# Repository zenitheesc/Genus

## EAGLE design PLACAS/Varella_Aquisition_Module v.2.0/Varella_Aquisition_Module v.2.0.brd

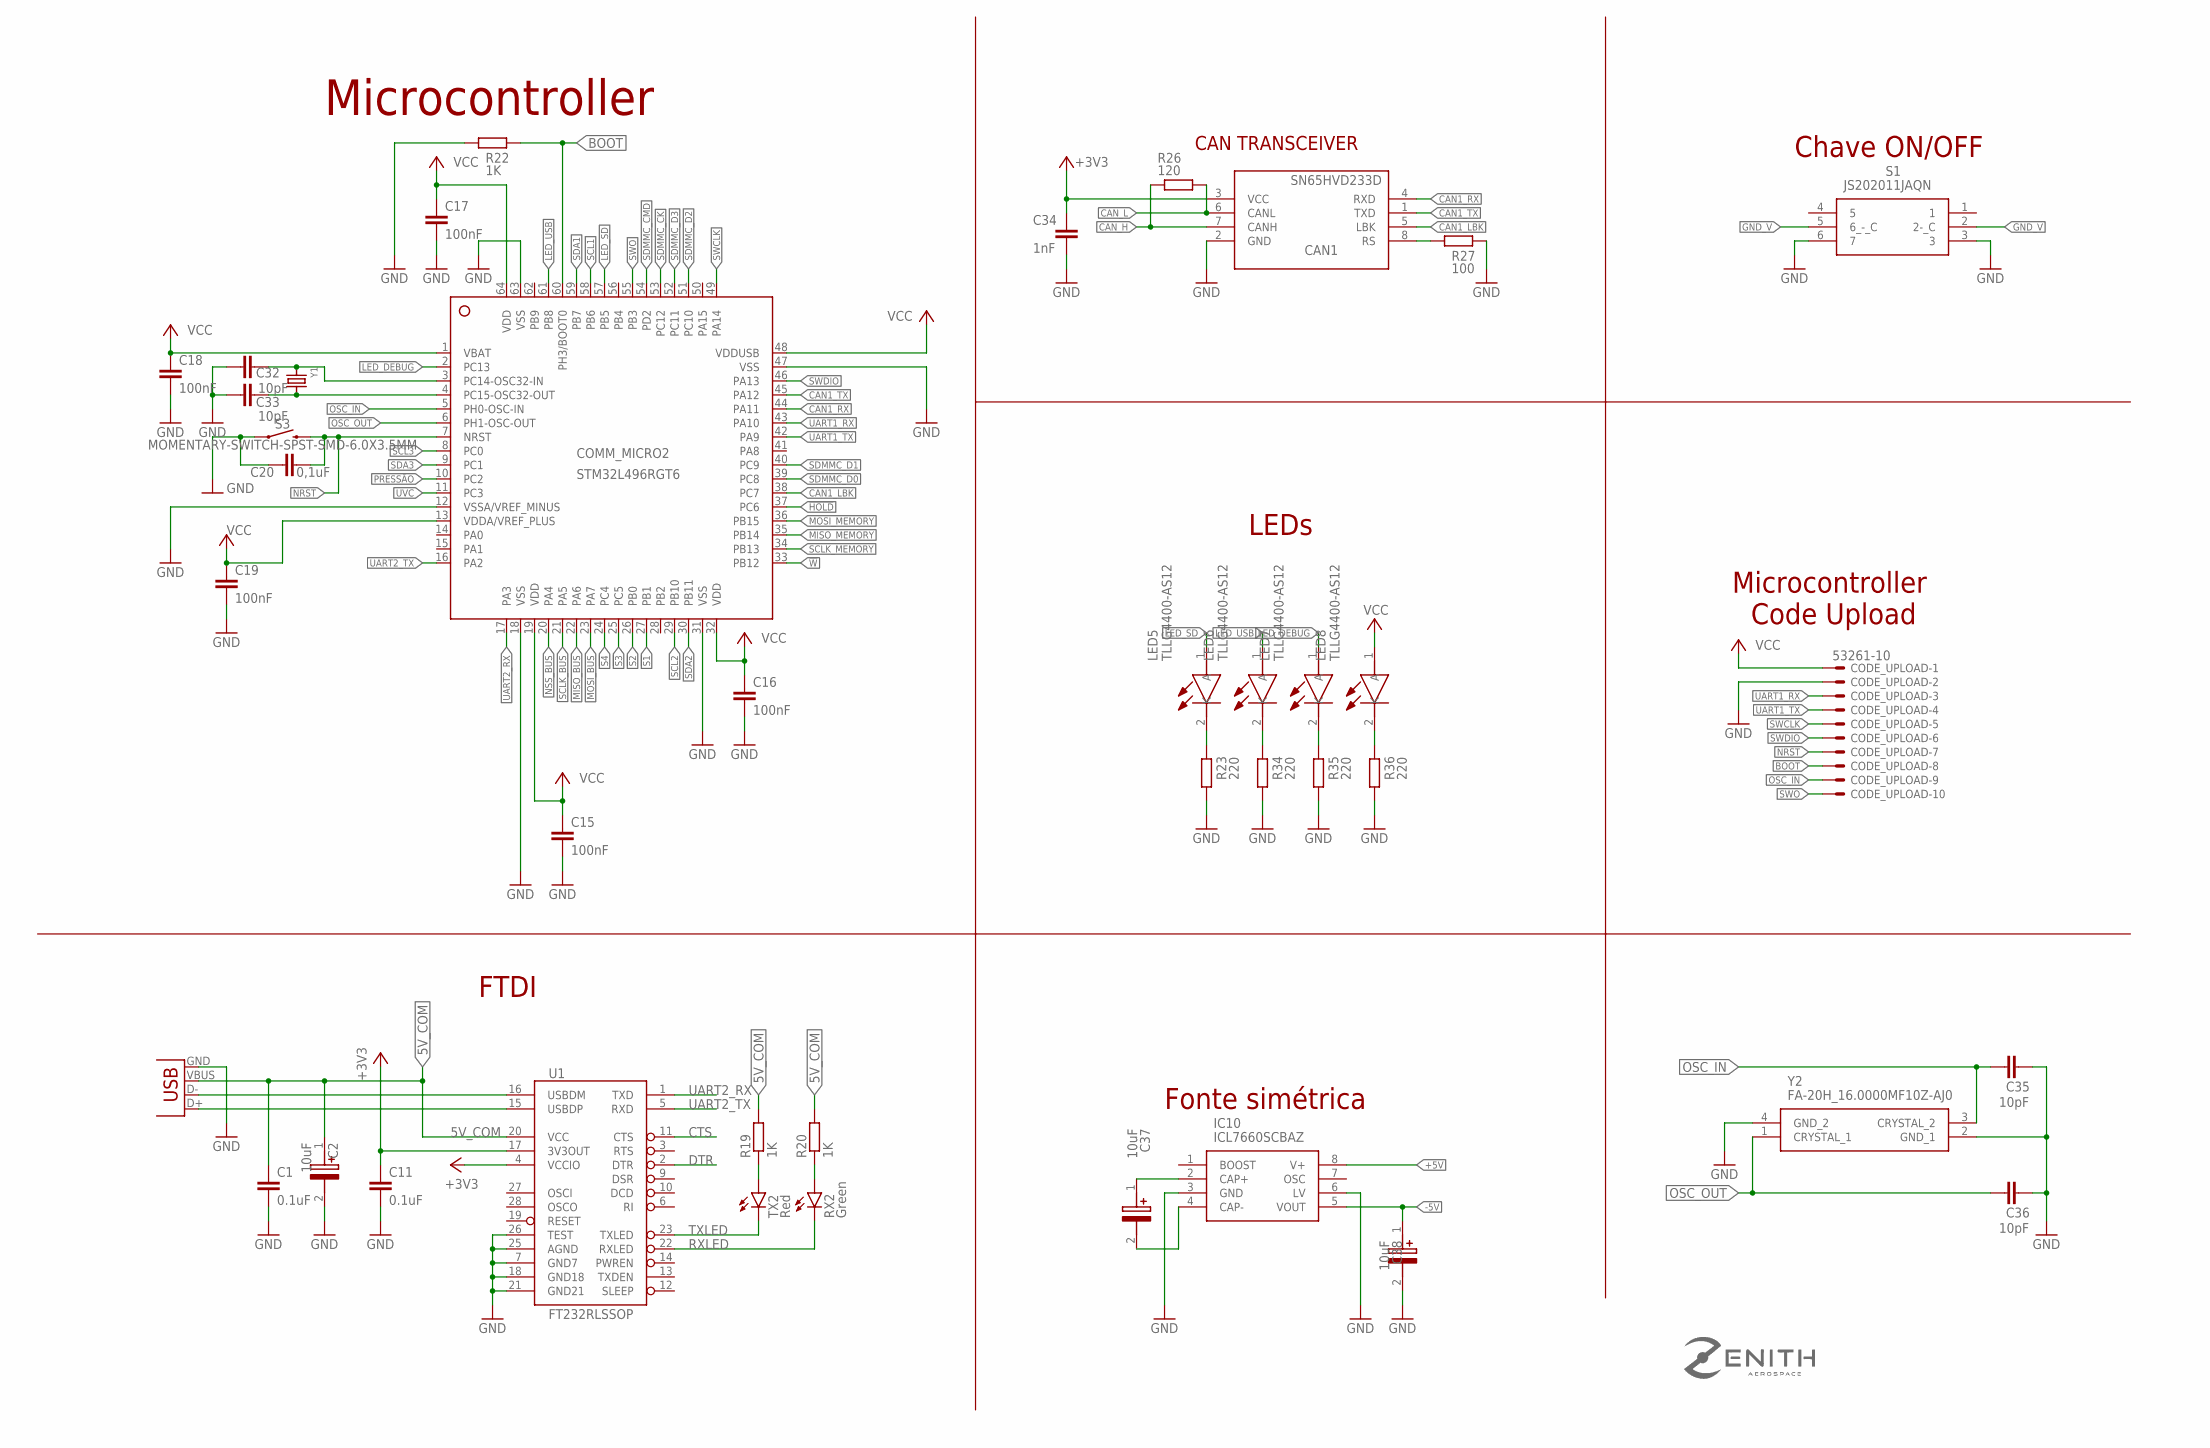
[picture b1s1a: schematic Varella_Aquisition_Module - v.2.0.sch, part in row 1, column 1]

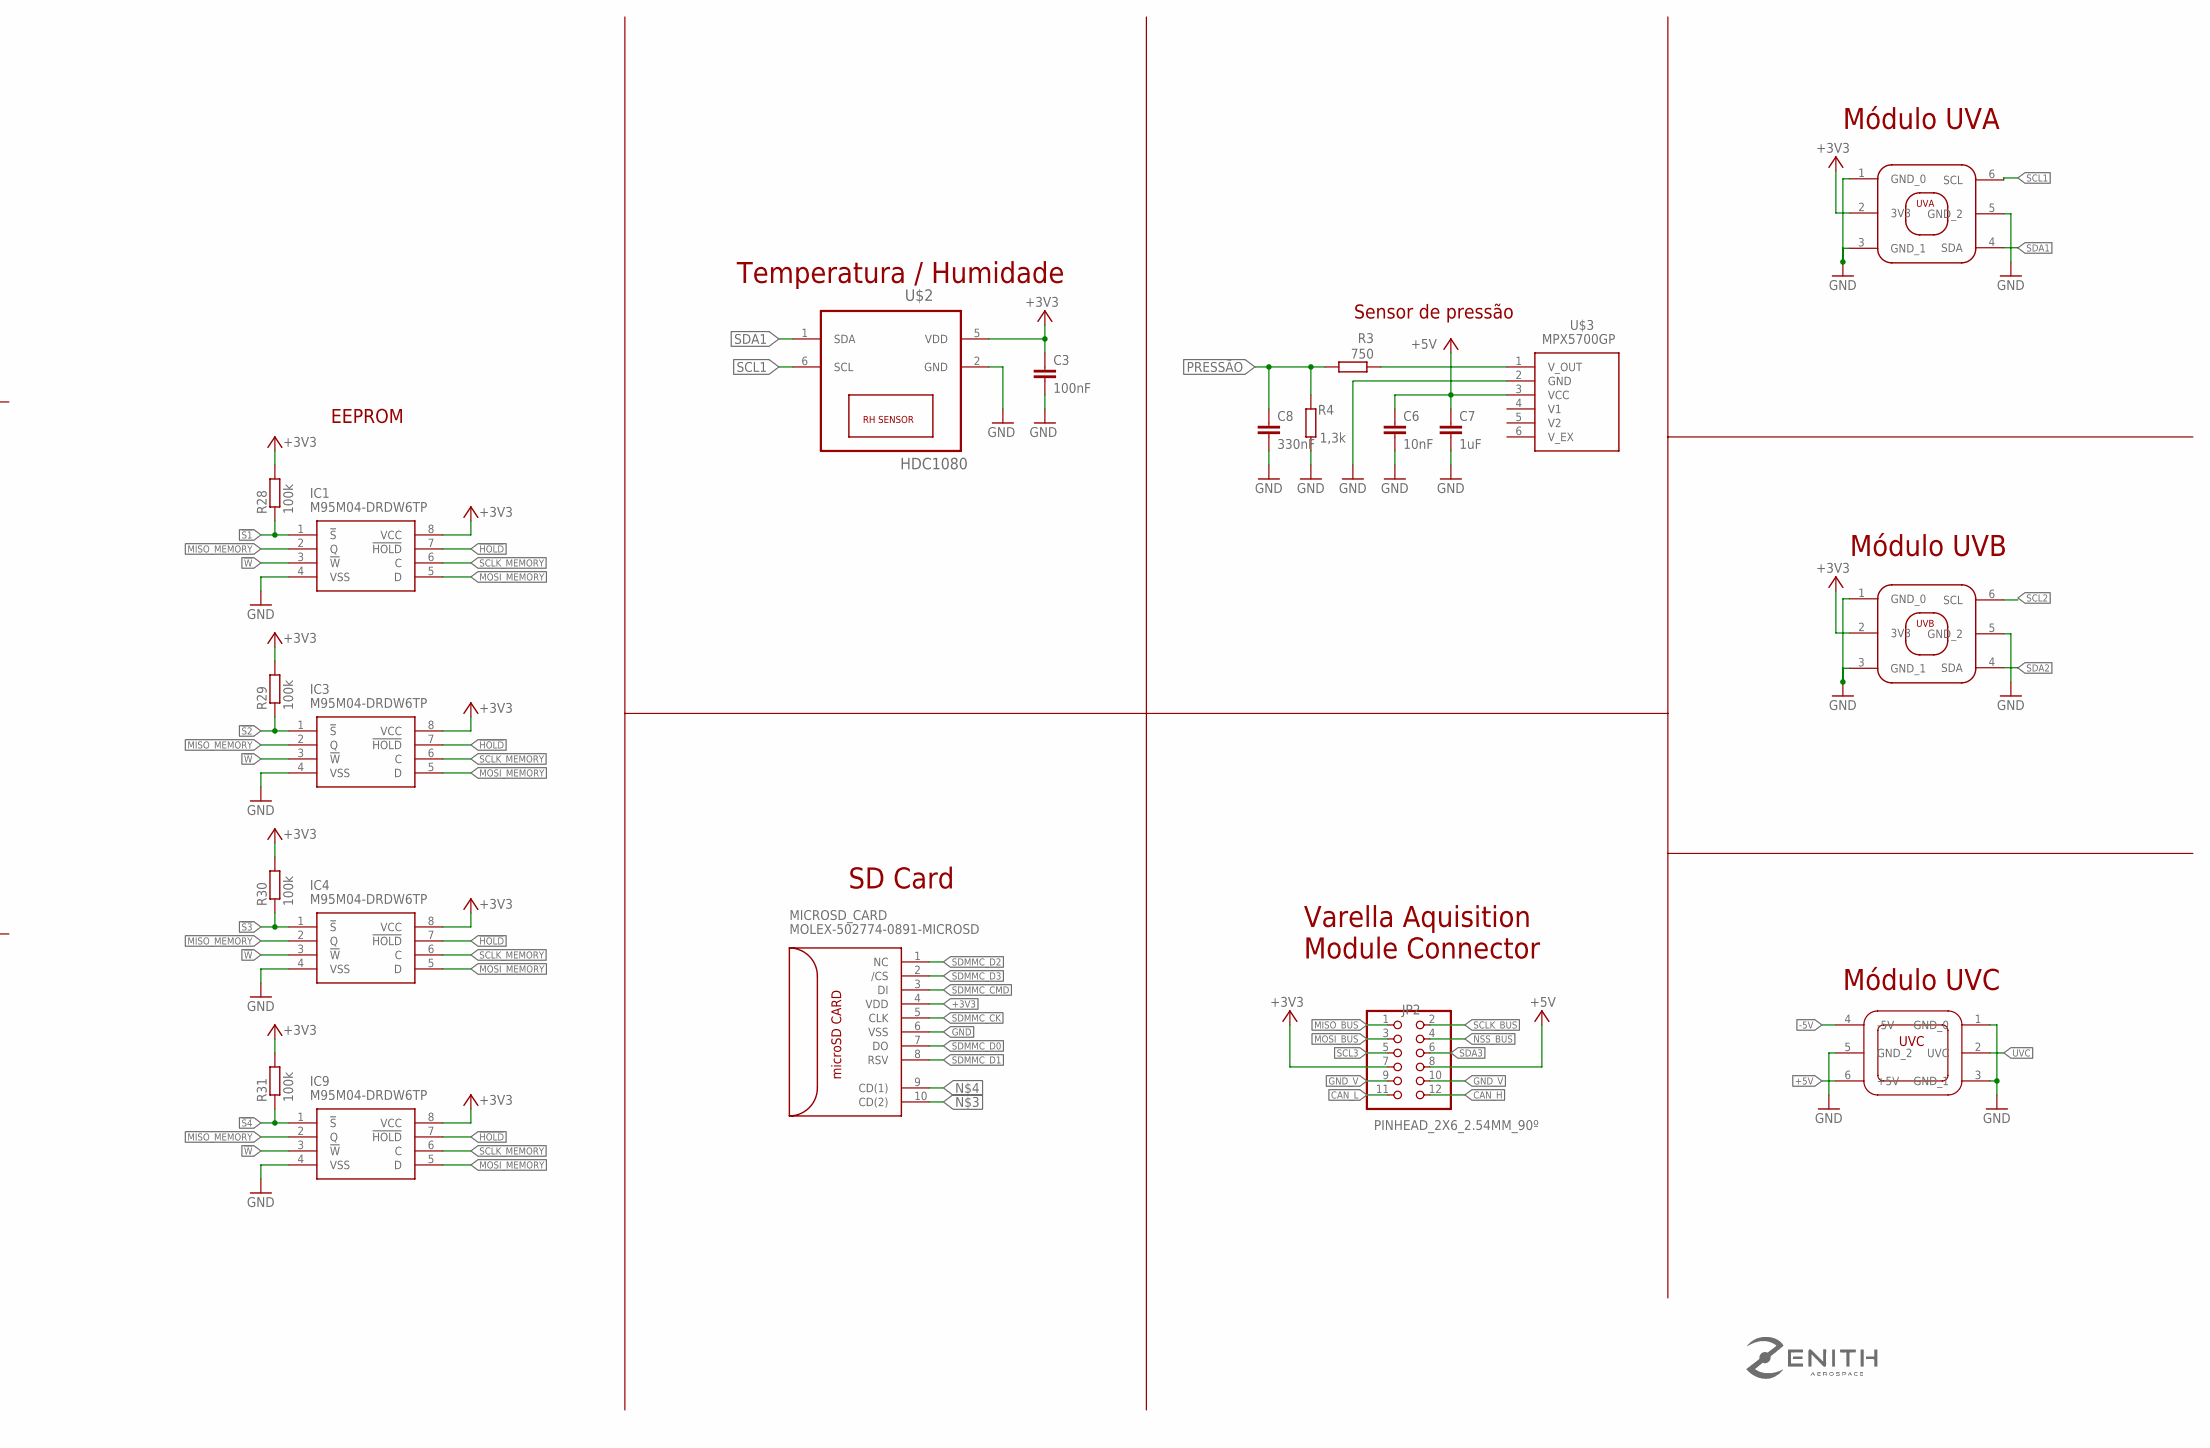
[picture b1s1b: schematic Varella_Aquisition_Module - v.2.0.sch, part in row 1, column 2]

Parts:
C1, C11: 0.1uF; C0805
C2, C37, C38: 10uF; CAPAE430X610N
C3, C15, C16, C17, C18, C19: 100nF; C0805
C6: 10nF; C0805
C7: 1uF; C0805
C8: 330nF; C0805
C20: 0,1uF; C0805
C32, C33, C35, C36: 10pF; C0805
C34: 1nF; C1206
CAN1: SN65HVD233D; SOIC8
CODE_UPLOAD: 53261-10
COMM_MICRO2: STM32L496RGT6; LQFP64_10X10
IC1, IC3, IC4, IC9: M95M04-DRDW6TP; SOP65P640X120-8N
IC10: ICL7660SCBAZ; SOIC127P600X175-8N@1
JP2: PINHEAD_2X6_2.54MM_90º
LED5, LED6, LED7, LED8: TLLG4400-AS12; TLLG4400AS12
MICROSD_CARD: MOLEX-502774-0891-MICROSD
R3: 750; R0805
R4: 1,3k; R0805
R19, R20, R22: 1K; R0805
R23, R34, R35, R36: 220; R0805
R26: 120; R1206
R27: 100; R0805
R28, R29, R30, R31: 100k; R0805
RX2: Green; CHIPLED_0805
S1: JS202011JAQN
S3: MOMENTARY-SWITCH-SPST-SMD-6.0X3.5MM; TACTILE_SWITCH_SMD_6.0X3.5MM
TX2: Red; CHIPLED_0805
U1: FT232RLSSOP; SSOP28DB
U$1: UVA_MODULE
U$2: HDC1080; TI-S-PWSON-N6
U$3: MPX5700GP
U$4: UVB_MODULE
U$5: UVC_MODULE
X2: USB-SMD-NS; USB-MINIB-NOSTOP
Y1: CRYSTAL8X3.8SMT; CRYSTAL_8X3.8
Y2: FA-20H_16.0000MF10Z-AJ0; FA20H160000MF12ZAC3

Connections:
5V_COM: C1.1, C2.1 (+), R19.2, R20.2, U1.20 (VCC), X2.VBUS
!HOLD: COMM_MICRO2.37 (PC6), IC1.7 (!HOLD), IC3.7 (!HOLD), IC4.7 (!HOLD), IC9.7 (!HOLD)
!S1: COMM_MICRO2.27 (PB1), IC1.1 (!S), R28.1
!S2: COMM_MICRO2.26 (PB0), IC3.1 (!S), R29.1
!S3: COMM_MICRO2.25 (PC5), IC4.1 (!S), R30.1
!S4: COMM_MICRO2.24 (PC4), IC9.1 (!S), R31.1
!W: COMM_MICRO2.33 (PB12), IC1.3 (!W), IC3.3 (!W), IC4.3 (!W), IC9.3 (!W)
+3V3: C3.1, C11.1, C15.1, C16.1, C17.1, C18.1, C19.1, C34.1, CAN1.3 (VCC), CODE_UPLOAD.1, COMM_MICRO2.1 (VBAT), COMM_MICRO2.13 (VDDA/VREF_PLUS), COMM_MICRO2.19 (VDD), COMM_MICRO2.32 (VDD), COMM_MICRO2.48 (VDDUSB), COMM_MICRO2.64 (VDD), IC1.8 (VCC), IC3.8 (VCC), IC4.8 (VCC), IC9.8 (VCC), JP2.7, LED8.1 (A), MICROSD_CARD.4 (VDD), R28.2, R29.2, R30.2, R31.2, U1.4 (VCCIO), U1.17 (3V3OUT), U$1.2 (3V3), U$2.5 (VDD), U$4.2 (3V3)
+5V: C6.1, C7.1, IC10.8 (V+), JP2.8, U$3.3 (VCC), U$5.6 (+5V)
-5V: C38.1 (+), IC10.5 (VOUT), U$5.4 (-5V)
BOOT: CODE_UPLOAD.8, COMM_MICRO2.60 (PH3/BOOT0), R22.1
CAN1_LBK: CAN1.5 (LBK), COMM_MICRO2.38 (PC7)
CAN1_RX: CAN1.4 (RXD), COMM_MICRO2.44 (PA11)
CAN1_TX: CAN1.1 (TXD), COMM_MICRO2.45 (PA12)
CAN_H: CAN1.7 (CANH), JP2.12, R26.1
CAN_L: CAN1.6 (CANL), JP2.11, R26.2
CRYSTAL1: C32.2, COMM_MICRO2.3 (PC14-OSC32-IN), Y1.P$1 (1)
CTS: U1.11 (CTS)
DTR: U1.2 (DTR)
GND: C1.2, C2.2 (-), C3.2, C6.2, C7.2, C8.2, C11.2, C15.2, C16.2, C17.2, C18.2, C19.2, C20.1, C32.1, C33.1, C34.2, C35.2, C36.2, C38.2 (-), CAN1.2 (GND), CODE_UPLOAD.2, COMM_MICRO2.12 (VSSA/VREF_MINUS), COMM_MICRO2.18 (VSS), COMM_MICRO2.31 (VSS), COMM_MICRO2.47 (VSS), COMM_MICRO2.63 (VSS), IC1.4 (VSS), IC3.4 (VSS), IC4.4 (VSS), IC9.4 (VSS), IC10.3 (GND), IC10.6 (LV), MICROSD_CARD.6 (VSS), R4.2, R22.2, R23.1, R27.1, R34.1, R35.1, R36.1, S1.3, S1.6 (7), S3.1, U1.7 (GND7), U1.18 (GND18), U1.21 (GND21), U1.25 (AGND), U1.26 (TEST), U$1.1 (GND_0), U$1.3 (GND_1), U$1.5 (GND_2), U$2.2 (GND), U$4.1 (GND_0), U$4.3 (GND_1), U$4.5 (GND_2), U$5.1 (GND_0), U$5.3 (GND_1), U$5.5 (GND_2), X2.GND, Y2.2 (GND_1), Y2.4 (GND_2)
GND_V: JP2.9, JP2.10, S1.2 (2-_C), S1.5 (6_-_C)
LED_DEBUG: COMM_MICRO2.2 (PC13), LED7.1 (A)
LED_SD: COMM_MICRO2.57 (PB5), LED5.1 (A)
LED_USB: COMM_MICRO2.61 (PB8), LED6.1 (A)
MISO_BUS: COMM_MICRO2.22 (PA6), JP2.1
MISO_MEMORY: COMM_MICRO2.35 (PB14), IC1.2 (Q), IC3.2 (Q), IC4.2 (Q), IC9.2 (Q)
MOSI_BUS: COMM_MICRO2.23 (PA7), JP2.3
MOSI_MEMORY: COMM_MICRO2.36 (PB15), IC1.5 (D), IC3.5 (D), IC4.5 (D), IC9.5 (D)
unnamed: R3.1, U$3.1 (V_OUT)
unnamed: C33.2, COMM_MICRO2.4 (PC15-OSC32-OUT), Y1.P$4 (2)
unnamed: CAN1.8 (RS), R27.2
unnamed: C37.1 (+), IC10.2 (CAP+)
unnamed: C37.2 (-), IC10.4 (CAP-)
unnamed: LED5.2 (K), R23.2
unnamed: LED6.2 (K), R34.2
unnamed: LED7.2 (K), R35.2
unnamed: LED8.2 (K), R36.2
NRST: C20.2, CODE_UPLOAD.7, COMM_MICRO2.7 (NRST), S3.2
NSS_BUS: COMM_MICRO2.20 (PA4), JP2.4
OSC_IN: C35.1, CODE_UPLOAD.9, COMM_MICRO2.5 (PH0-OSC-IN), Y2.3 (CRYSTAL_2)
OSC_OUT: C36.1, COMM_MICRO2.6 (PH1-OSC-OUT), Y2.1 (CRYSTAL_1)
PRESSÃO: C8.1, COMM_MICRO2.10 (PC2), R3.2, R4.1
RXL: R20.1, RX2.A
RXLED: RX2.C, U1.22 (RXLED)
SCL1: COMM_MICRO2.58 (PB6), U$1.6 (SCL), U$2.6 (SCL)
SCL2: COMM_MICRO2.29 (PB10), U$4.6 (SCL)
SCL3: COMM_MICRO2.8 (PC0), JP2.5
SCLK_BUS: COMM_MICRO2.21 (PA5), JP2.2
SCLK_MEMORY: COMM_MICRO2.34 (PB13), IC1.6 (C), IC3.6 (C), IC4.6 (C), IC9.6 (C)
SDA1: COMM_MICRO2.59 (PB7), U$1.4 (SDA), U$2.1 (SDA)
SDA2: COMM_MICRO2.30 (PB11), U$4.4 (SDA)
SDA3: COMM_MICRO2.9 (PC1), JP2.6
SDMMC_CK: COMM_MICRO2.53 (PC12), MICROSD_CARD.5 (CLK)
SDMMC_CMD: COMM_MICRO2.54 (PD2), MICROSD_CARD.3 (DI)
SDMMC_D0: COMM_MICRO2.39 (PC8), MICROSD_CARD.7 (DO)
SDMMC_D1: COMM_MICRO2.40 (PC9), MICROSD_CARD.8 (RSV)
SDMMC_D2: COMM_MICRO2.51 (PC10), MICROSD_CARD.1 (NC)
SDMMC_D3: COMM_MICRO2.52 (PC11), MICROSD_CARD.2 (/CS)
SWCLK: CODE_UPLOAD.5, COMM_MICRO2.49 (PA14)
SWDIO: CODE_UPLOAD.6, COMM_MICRO2.46 (PA13)
SWO: CODE_UPLOAD.10, COMM_MICRO2.55 (PB3)
TXL: R19.1, TX2.A
TXLED: TX2.C, U1.23 (TXLED)
UART1_RX: CODE_UPLOAD.3, COMM_MICRO2.43 (PA10)
UART1_TX: CODE_UPLOAD.4, COMM_MICRO2.42 (PA9)
UART2_RX: COMM_MICRO2.17 (PA3), U1.1 (TXD)
UART2_TX: COMM_MICRO2.16 (PA2), U1.5 (RXD)
USB_D+2: U1.15 (USBDP), X2.D+
USB_D-2: U1.16 (USBDM), X2.D-
UVC: COMM_MICRO2.11 (PC3), U$5.2 (UVC)

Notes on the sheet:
C:/Users/marcu/Desktop/Ensino Superior/Graduação - Eng Elétrica/Zenith/zenith-v2.bmp
Microcontroller
CAN TRANSCEIVER
Microcontroller Code Upload
SD Card
Varella Aquisition Module Connector
EEPROM
FTDI
Temperatura / Humidade
Fonte simétrica
LEDs
Sensor de pressão
Chave ON/OFF
Módulo UVA
Módulo UVB
Módulo UVC

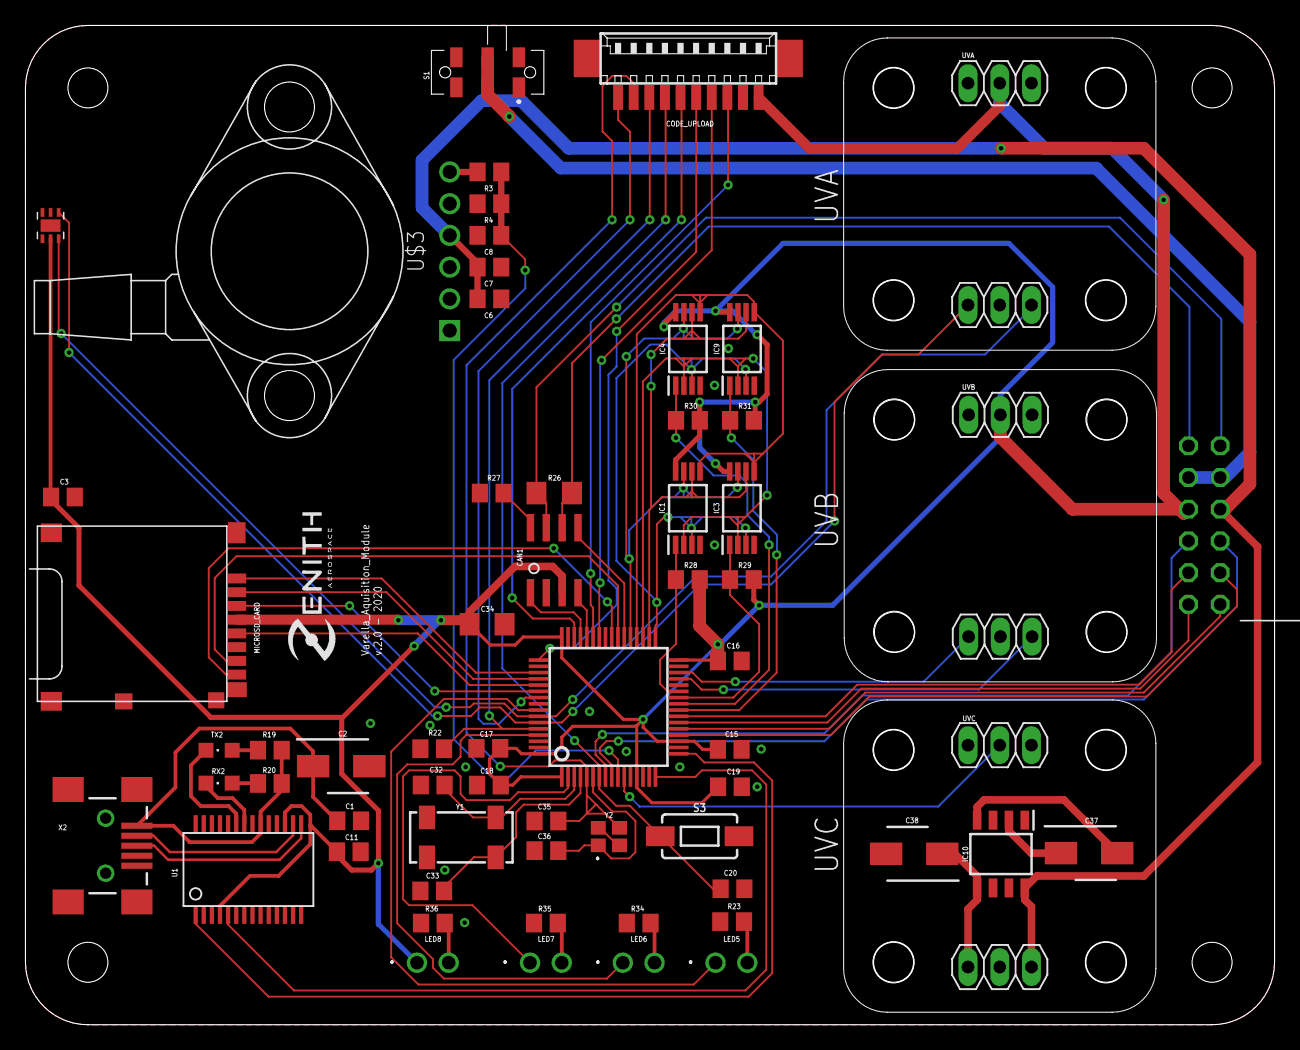
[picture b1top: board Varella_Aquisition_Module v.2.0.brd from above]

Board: 2 copper layers, 100.0 x 80.0 mm, 62 parts (1 on the bottom side), 68 nets.

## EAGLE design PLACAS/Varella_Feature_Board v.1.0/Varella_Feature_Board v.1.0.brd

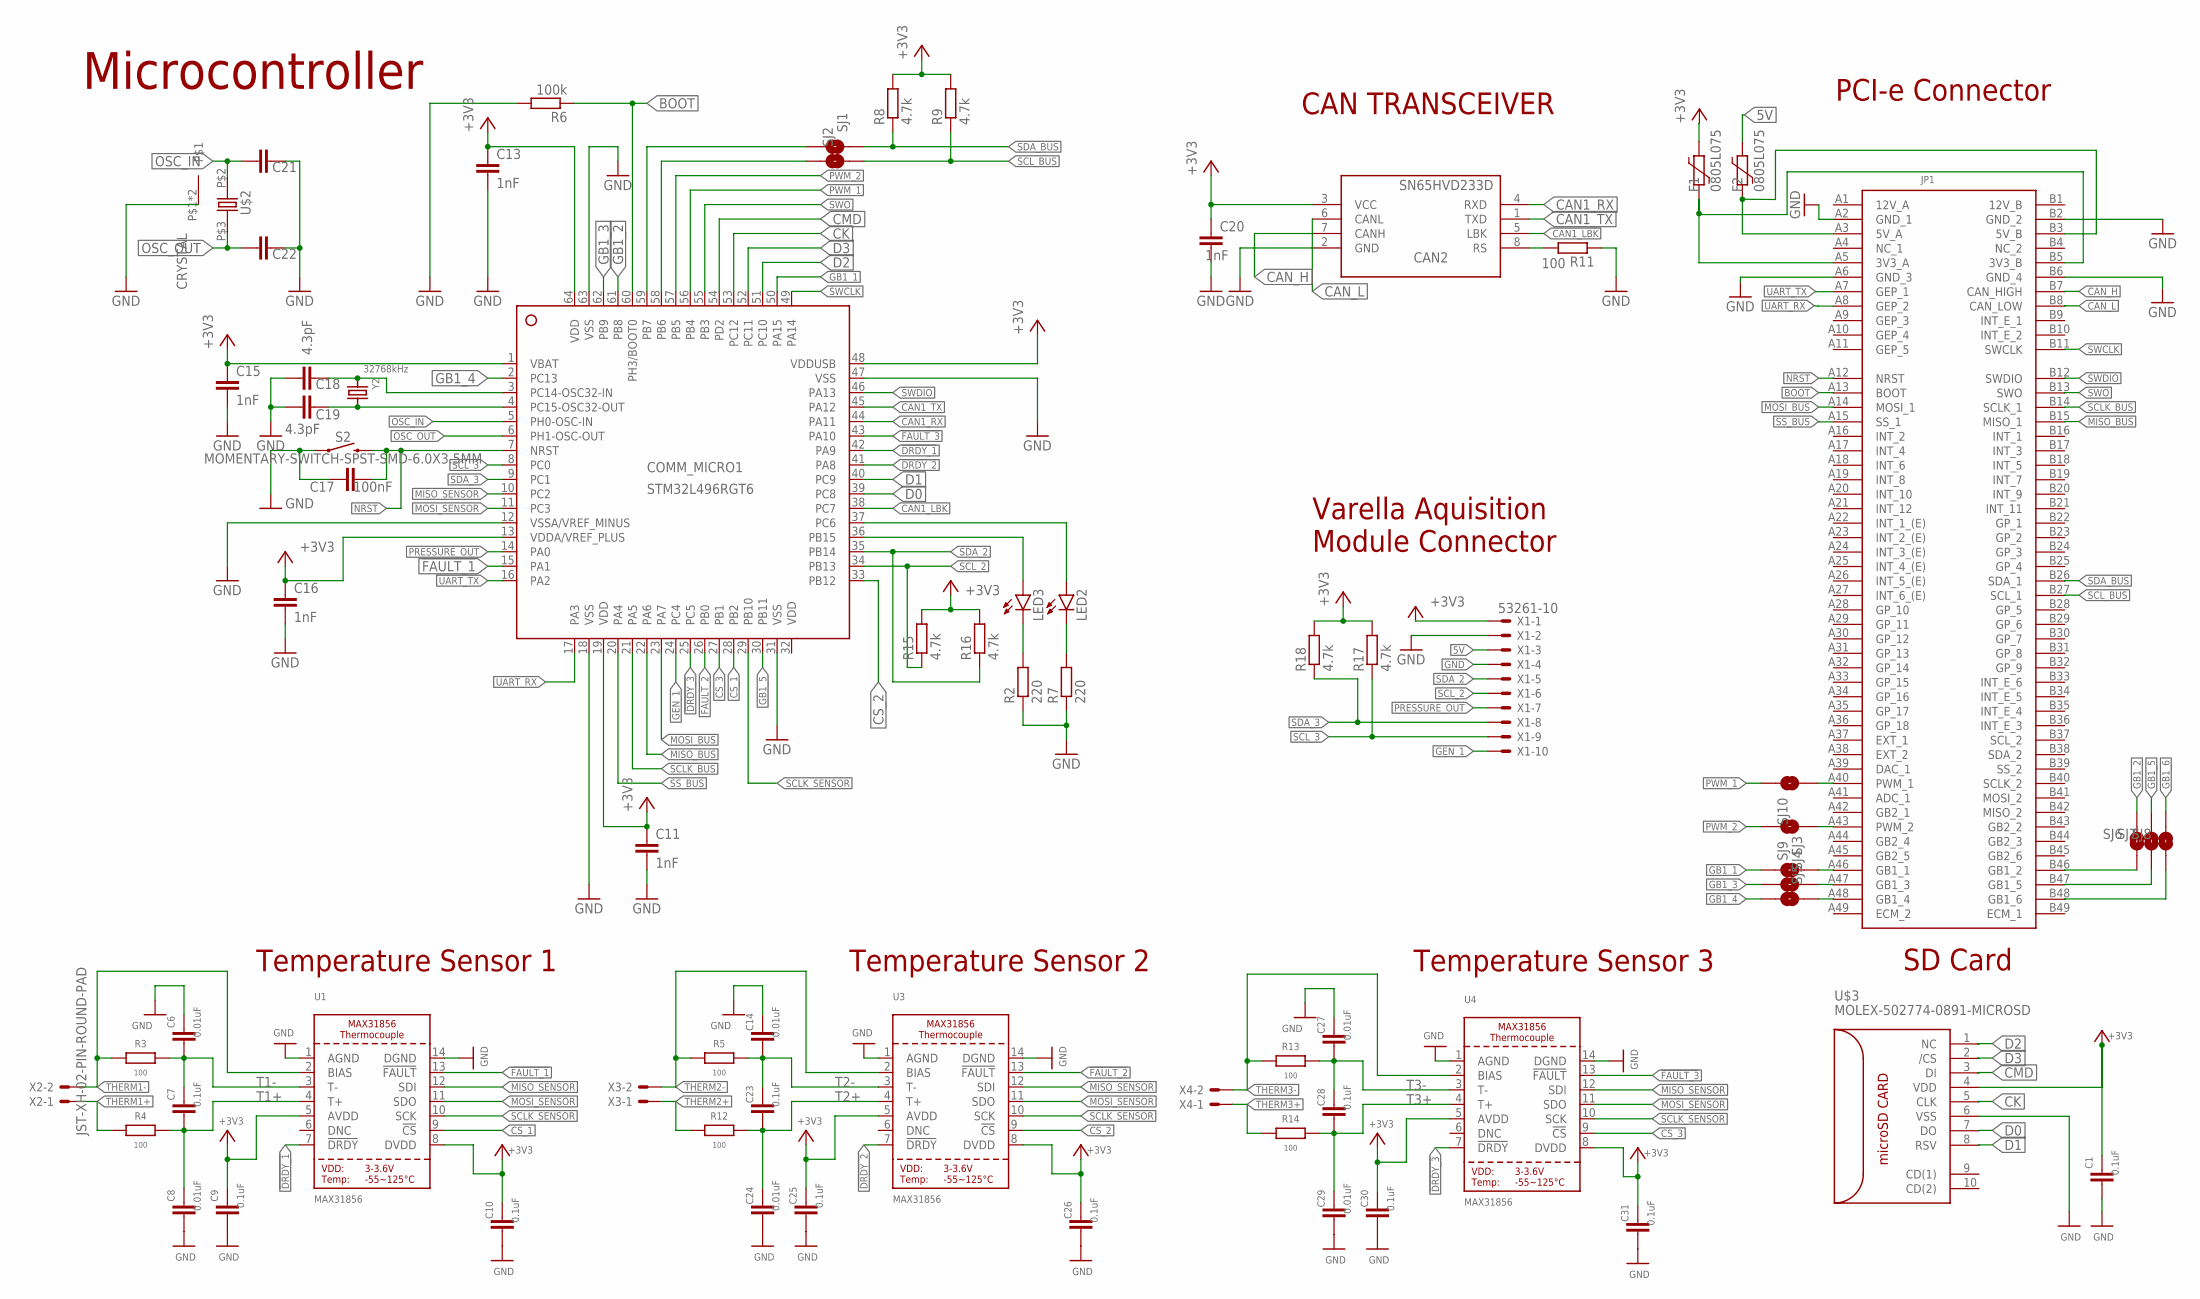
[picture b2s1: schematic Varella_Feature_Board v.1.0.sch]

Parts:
C1, C7, C9, C10, C23, C25, C26, C28, C30, C31: 0.1uF; C0805
C6, C8, C14, C24, C27, C29: 0.01uF; C0805
C11, C13, C15, C16, C20: 1nF; C0805
C17: 100nF; C0805
C18, C19: 4.3pF; C0805
C21, C22: C-EUC0805; C0805
CAN2: SN65HVD233D; SOIC8
COMM_MICRO1: STM32L496RGT6; LQFP64_10X10
F1, F2: 0805L075; 0805L
JP1: FEATURE_BOARD; PCI-E_164_EDGE
LED2, LED3: LEDCHIP-LED0805; CHIP-LED0805
R2, R7: 220; R0805
R3, R4, R5, R11, R12, R13, R14: 100; R0805
R6: 100k; R0805
R8, R9, R15, R16, R17, R18: 4.7k; R0805
S2: MOMENTARY-SWITCH-SPST-SMD-6.0X3.5MM; TACTILE_SWITCH_SMD_6.0X3.5MM
SJ1, SJ2, SJ3, SJ4, SJ5, SJ6, SJ7, SJ8, SJ9, SJ10: SMD-JUMPER-2
U1, U3, U4: MAX31856; TSSOP14
U$2: CRYSTAL; CRYSTAL_SMD
U$3: MOLEX-502774-0891-MICROSD
X1: 53261-10
X2, X3, X4: JST-XH-02-PIN-ROUND-PAD; JST-XH-02-PACKAGE-ROUND-PAD
Y2: 32768kHz; CRYSTAL_8X3.8

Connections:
3.3V: C9.1, C10.1, C25.1, C26.1, C30.1, C31.1, U1.5 (AVDD), U1.8 (DVDD), U3.5 (AVDD), U3.8 (DVDD), U4.5 (AVDD), U4.8 (DVDD)
5V: F2.1, X1.3
12V_A: JP1.A1 (12V_A)
12V_B: JP1.B1 (12V_B)
!DRDY_1: COMM_MICRO1.42 (PA9), U1.7 (!DRDY)
!DRDY_2: COMM_MICRO1.41 (PA8), U3.7 (!DRDY)
!DRDY_3: COMM_MICRO1.25 (PC5), U4.7 (!DRDY)
!FAULT_1: COMM_MICRO1.15 (PA1), U1.13 (!FAULT)
!FAULT_2: COMM_MICRO1.26 (PB0), U3.13 (!FAULT)
!FAULT_3: COMM_MICRO1.43 (PA10), U4.13 (!FAULT)
+3V3: C1.1, C11.1, C13.1, C15.1, C16.1, C20.1, CAN2.3 (VCC), COMM_MICRO1.1 (VBAT), COMM_MICRO1.13 (VDDA/VREF_PLUS), COMM_MICRO1.19 (VDD), COMM_MICRO1.48 (VDDUSB), COMM_MICRO1.64 (VDD), F1.1, R8.2, R9.2, R15.2, R16.2, R17.2, R18.2, U$3.4 (VDD), X1.1
BOOT: COMM_MICRO1.60 (PH3/BOOT0), JP1.A13 (BOOT), R6.1
CAN1_LBK: CAN2.5 (LBK), COMM_MICRO1.38 (PC7)
CAN1_RX: CAN2.4 (RXD), COMM_MICRO1.44 (PA11)
CAN1_TX: CAN2.1 (TXD), COMM_MICRO1.45 (PA12)
CAN_H: CAN2.7 (CANH), JP1.B7 (CAN_HIGH)
CAN_L: CAN2.6 (CANL), JP1.B8 (CAN_LOW)
CK: COMM_MICRO1.53 (PC12), U$3.5 (CLK)
CMD: COMM_MICRO1.54 (PD2), U$3.3 (DI)
CS_1: COMM_MICRO1.28 (PB2), U1.9 (!CS)
CS_2: COMM_MICRO1.33 (PB12), U3.9 (!CS)
CS_3: COMM_MICRO1.27 (PB1), U4.9 (!CS)
D0: COMM_MICRO1.39 (PC8), U$3.7 (DO)
D1: COMM_MICRO1.40 (PC9), U$3.8 (RSV)
D2: COMM_MICRO1.51 (PC10), U$3.1 (NC)
D3: COMM_MICRO1.52 (PC11), U$3.2 (/CS)
GB1_1: COMM_MICRO1.50 (PA15), SJ3.1
GB1_2: COMM_MICRO1.61 (PB8), SJ6.2
GB1_3: COMM_MICRO1.62 (PB9), SJ4.1
GB1_4: COMM_MICRO1.2 (PC13), SJ5.1
GB1_5: COMM_MICRO1.30 (PB11), SJ7.2
GB1_6: SJ8.2
GEN_1: COMM_MICRO1.24 (PC4), X1.10
GND: C1.2, C6.1, C8.2, C9.2, C10.2, C11.2, C13.2, C14.1, C15.2, C16.2, C17.1, C18.1, C19.1, C20.2, C21.2, C22.2, C24.2, C25.2, C26.2, C27.1, C29.2, C30.2, C31.2, CAN2.2 (GND), COMM_MICRO1.12 (VSSA/VREF_MINUS), COMM_MICRO1.18 (VSS), COMM_MICRO1.31 (VSS), COMM_MICRO1.47 (VSS), COMM_MICRO1.63 (VSS), JP1.A2 (GND_1), JP1.A6 (GND_3), JP1.B2 (GND_2), R2.1, R6.2, R7.1, R11.1, S2.1, U1.1 (AGND), U1.14 (DGND), U3.1 (AGND), U3.14 (DGND), U4.1 (AGND), U4.14 (DGND), U$2.P$1, U$2.P$4, U$3.6 (VSS), X1.2, X1.4
GND(6): JP1.B6 (GND_4)
MISO_BUS: COMM_MICRO1.22 (PA6), JP1.B15 (MISO_1)
MISO_SENSOR: COMM_MICRO1.10 (PC2), U1.12 (SDI), U3.12 (SDI), U4.12 (SDI)
MOSI_BUS: COMM_MICRO1.23 (PA7), JP1.A14 (MOSI_1)
MOSI_SENSOR: COMM_MICRO1.11 (PC3), U1.11 (SDO), U3.11 (SDO), U4.11 (SDO)
unnamed: JP1.A40 (PWM_1), JP1.A43 (PWM_2), SJ9.1, SJ10.1
unnamed: JP1.A47 (GB1_3), SJ4.2
unnamed: COMM_MICRO1.36 (PB15), LED3.A
unnamed: LED3.C, R2.2
unnamed: F2.2, JP1.A3 (5V_A), JP1.B3 (5V_B)
unnamed: COMM_MICRO1.37 (PC6), LED2.A
unnamed: LED2.C, R7.2
unnamed: F1.2, JP1.A5 (3V3_A), JP1.B5 (3V3_B)
unnamed: JP1.B46 (GB1_2), SJ6.1
unnamed: C18.2, COMM_MICRO1.3 (PC14-OSC32-IN), Y2.P$1 (1)
unnamed: C19.2, COMM_MICRO1.4 (PC15-OSC32-OUT), Y2.P$4 (2)
unnamed: COMM_MICRO1.59 (PB7), SJ1.1
unnamed: COMM_MICRO1.58 (PB6), SJ2.1
unnamed: CAN2.8 (RS), R11.2
unnamed: JP1.B47 (GB1_5), SJ7.1
unnamed: JP1.B48 (GB1_6), SJ8.1
unnamed: JP1.A48 (GB1_4), SJ5.2
unnamed: JP1.A46 (GB1_1), SJ3.2
NRST: C17.2, COMM_MICRO1.7 (NRST), JP1.A12 (NRST), S2.2
OSC_IN: C21.1, COMM_MICRO1.5 (PH0-OSC-IN), U$2.P$2 (1)
OSC_OUT: C22.1, COMM_MICRO1.6 (PH1-OSC-OUT), U$2.P$3 (2)
PRESSURE_OUT: COMM_MICRO1.14 (PA0), X1.7
PWM_1: COMM_MICRO1.56 (PB4), SJ10.2
PWM_2: COMM_MICRO1.57 (PB5), SJ9.2
SCLK_BUS: COMM_MICRO1.21 (PA5), JP1.B14 (SCLK_1)
SCLK_SENSOR: COMM_MICRO1.29 (PB10), U1.10 (SCK), U3.10 (SCK), U4.10 (SCK)
SCL_2: COMM_MICRO1.34 (PB13), R15.1, X1.6
SCL_3: COMM_MICRO1.8 (PC0), R17.1, X1.9
SCL_BUS: JP1.B27 (SCL_1), R9.1, SJ2.2
SDA_2: COMM_MICRO1.35 (PB14), R16.1, X1.5
SDA_3: COMM_MICRO1.9 (PC1), R18.1, X1.8
SDA_BUS: JP1.B26 (SDA_1), R8.1, SJ1.2
SS_BUS: COMM_MICRO1.20 (PA4), JP1.A15 (SS_1)
SWCLK: COMM_MICRO1.49 (PA14), JP1.B11 (SWCLK)
SWDIO: COMM_MICRO1.46 (PA13), JP1.B12 (SWDIO)
SWO: COMM_MICRO1.55 (PB3), JP1.B13 (SWO)
T1+: C7.2, C8.1, R4.2, U1.4 (T+)
T1-: C6.2, C7.1, R3.2, U1.3 (T-)
T2+: C23.2, C24.1, R12.2, U3.4 (T+)
T2-: C14.2, C23.1, R5.2, U3.3 (T-)
T3+: C28.2, C29.1, R14.2, U4.4 (T+)
T3-: C27.2, C28.1, R13.2, U4.3 (T-)
THERM1+: R4.1, X2.1
THERM1-: R3.1, U1.2 (BIAS), X2.2
THERM2+: R12.1, X3.1
THERM2-: R5.1, U3.2 (BIAS), X3.2
THERM3+: R14.1, X4.1
THERM3-: R13.1, U4.2 (BIAS), X4.2
UART_RX: COMM_MICRO1.17 (PA3), JP1.A8 (GEP_2)
UART_TX: COMM_MICRO1.16 (PA2), JP1.A7 (GEP_1)
VDD: COMM_MICRO1.32 (VDD)

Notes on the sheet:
Microcontroller
CAN TRANSCEIVER
Varella Aquisition Module Connector
Temperature Sensor 1
Temperature Sensor 2
Temperature Sensor 3
PCI-e Connector
SD Card

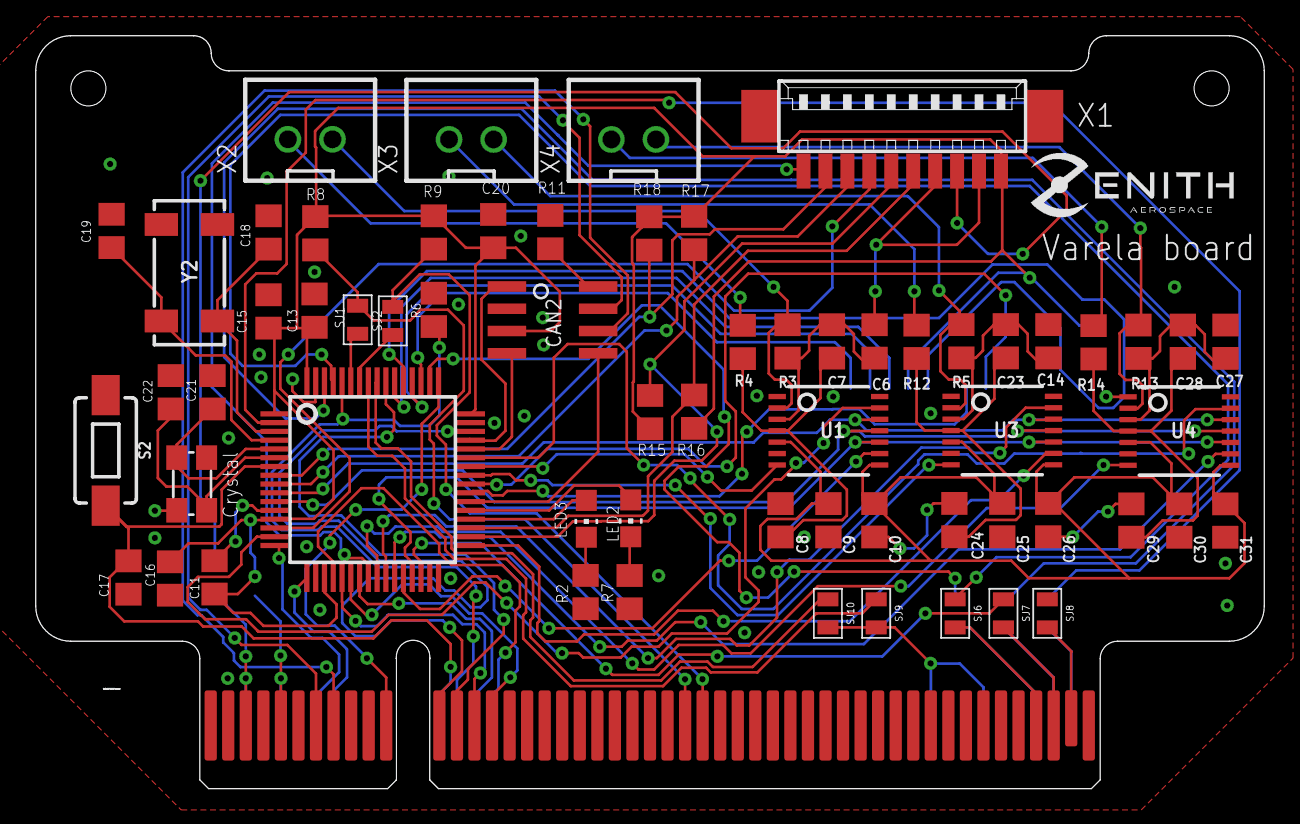
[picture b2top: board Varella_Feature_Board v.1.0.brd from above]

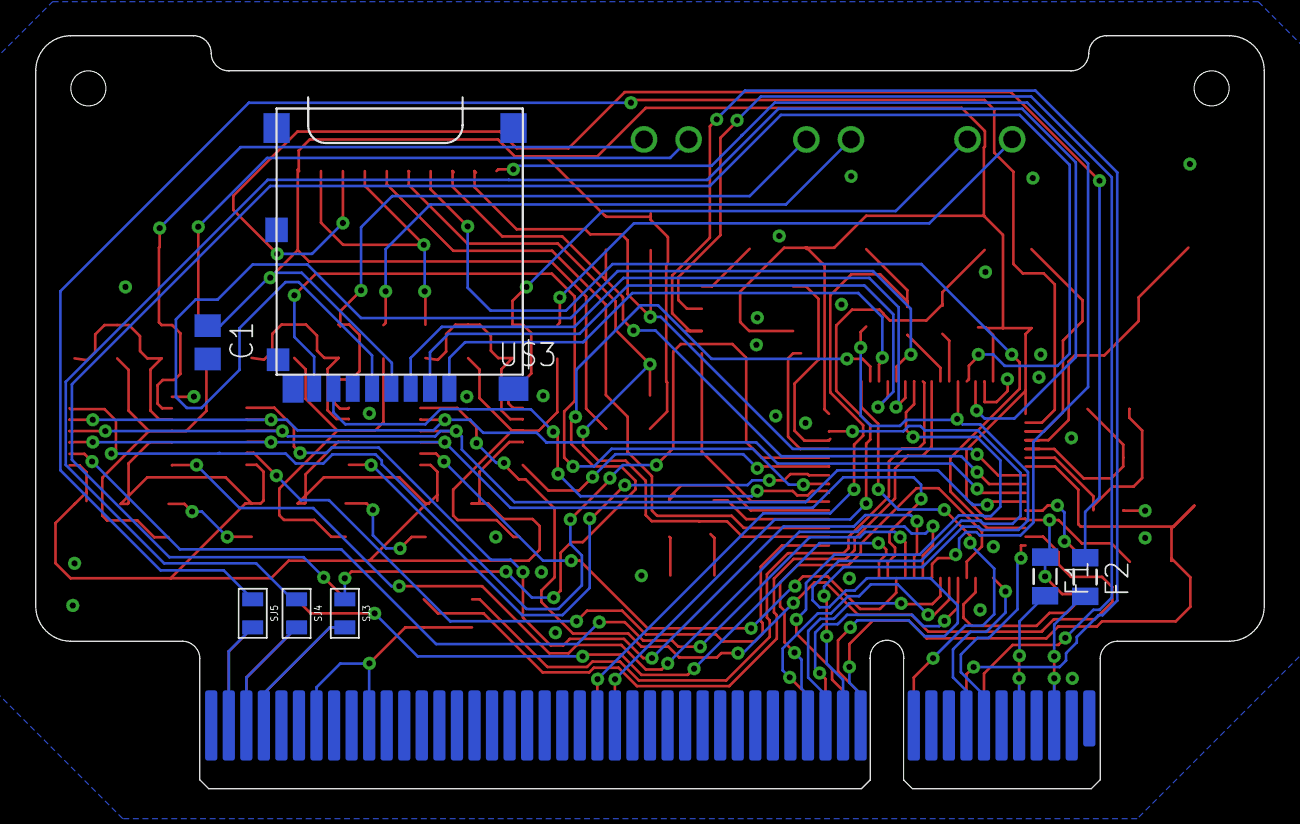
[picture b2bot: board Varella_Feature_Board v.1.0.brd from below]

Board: 2 copper layers, 70.0 x 42.9 mm, 70 parts (7 on the bottom side), 85 nets.

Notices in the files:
parts and their libraries:
SparkFun-Switches: Licensing: Creative Commons ShareAlike 4.0 International - https://creativecommons.org/licenses/by-sa/4.0
microbuilder: This work is placed in the public domain, and may be freely used for commercial and non-commercial work with the following conditions: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
